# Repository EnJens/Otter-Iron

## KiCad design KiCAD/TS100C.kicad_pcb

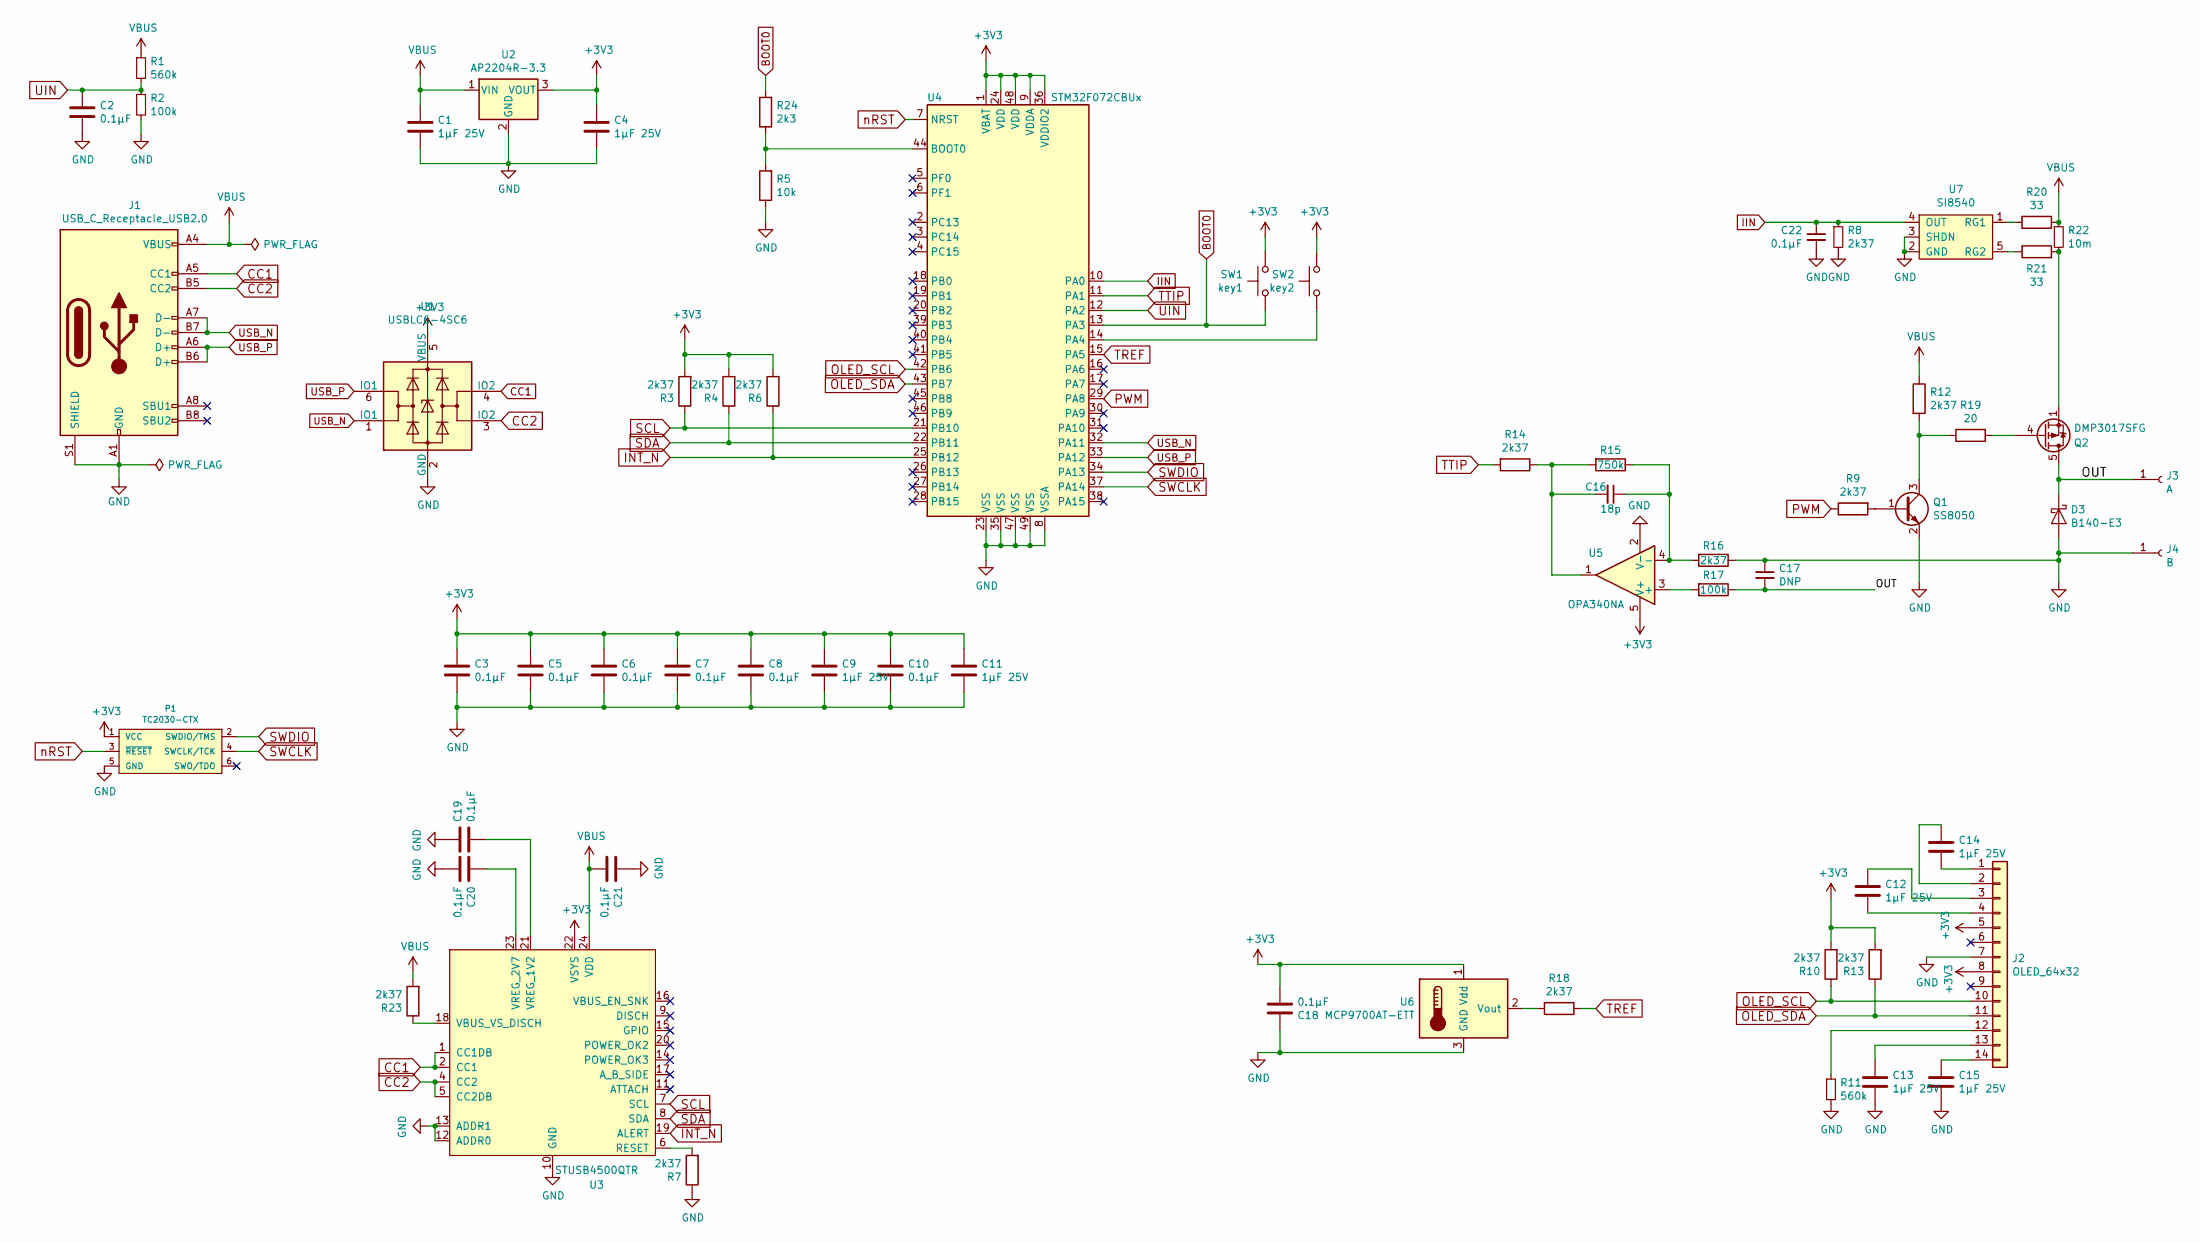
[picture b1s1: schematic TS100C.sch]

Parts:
C1, C4, C9, C11: 1μF 25V; C_0603_1608Metric
C2, C3, C5, C6, C7, C8, C10, C18, C19, C20, C21, C22: 0.1μF; C_0402_1005Metric
C12, C13, C14, C15: 1μF 25V; C_0402_1005Metric
C16: 18p; C_0402_1005Metric
C17: DNP; C_0402_1005Metric
D3: B140-E3; D_SOD-123F
J1: USB_C_Receptacle_USB2.0; USB-C 16Pin
J2: OLED_64x32; 0.69OLED
J3: A; Keystone_3621
J4: B; 3622TR
P1: TC2030-CTX; TC2030-NL_SMALL
Q1: SS8050; SOT-23
Q2: DMP3017SFG; Diodes_PowerDI3333-8
R1, R11: 560k; R_0402_1005Metric
R2, R17: 100k; R_0402_1005Metric
R3, R4, R6, R7, R8, R9, R10, R12, R13, R14, R16, R18, R23: 2k37; R_0402_1005Metric
R5: 10k; R_0402_1005Metric
R15: 750k; R_0402_1005Metric
R19: 20; R_0402_1005Metric
R20, R21: 33; R_0402_1005Metric
R22: 10m; R_0805_2012Metric
R24: 2k3; R_0402_1005Metric
SW1: key1; SW_SPST_PTS810
SW2: key2; SW_SPST_PTS810
U1: USBLC6-4SC6; SOT-23-6
U2: AP2204R-3.3; SOT-89-3
U3: STUSB4500QTR; QFN-24-1EP_4x4mm_P0.5mm_EP2.7x2.7mm
U4: STM32F072CBUx; QFN-48-1EP_7x7mm_P0.5mm_EP5.6x5.6mm
U5: OPA340NA; SOT-23-5
U6: MCP9700AT-ETT; SOT-23
U7: SI8540; SOT-23-5

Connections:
+3V3: C3.1, C4.1, C5.1, C6.1, C7.1, C8.1, C9.1, C10.1, C11.1, C18.1, J2.5, J2.8, P1.1 (VCC), R3.2, R4.2, R6.2, R10.2, R13.2, SW1.1, SW2.1, U1.5 (VBUS), U2.3 (VOUT), U3.22 (VSYS), U4.1 (VBAT), U4.9 (VDDA), U4.24 (VDD), U4.36 (VDDIO2), U4.48 (VDD), U5.5 (V+), U6.1 (Vdd)
/OUT: C17.2, D3.1 (K), J3.1, Q2.5 (D), R17.1
BOOT0: R24.2, SW1.2, U4.13 (PA3)
CC1: J1.A5 (CC1), U1.4 (IO2), U3.1 (CC1DB), U3.2 (CC1)
CC2: J1.B5 (CC2), U1.3 (IO2), U3.4 (CC2), U3.5 (CC2DB)
GND: C1.2, C2.2, C3.2, C4.2, C5.2, C6.2, C7.2, C8.2, C9.2, C10.2, C11.2, C13.2, C15.2, C17.1, C18.2, C19.1, C20.2, C21.1, C22.2, D3.2 (A), J1.A1 (GND), J1.A12 (GND), J1.B1 (GND), J1.B12 (GND), J1.S1 (SHIELD), J2.7, J4.1, P1.5 (GND), Q1.2 (E), R2.2, R5.1, R7.1, R8.2, R11.2, R16.1, U1.2 (GND), U2.2 (GND), U3.10 (GND), U3.12 (ADDR0), U3.13 (ADDR1), U3.25 (GND), U4.8 (VSSA), U4.23 (VSS), U4.35 (VSS), U4.47 (VSS), U4.49 (VSS), U5.2 (V-), U6.3 (GND), U7.2 (GND), U7.3 (SHDN)
IIN: C22.1, R8.1, U4.10 (PA0), U7.4 (OUT)
INT_N: R6.1, U3.19 (ALERT), U4.25 (PB12)
unnamed: C12.1, J2.3
unnamed: C12.2, J2.4
unnamed: C13.1, J2.13
unnamed: C14.1, J2.2
unnamed: C14.2, J2.1
unnamed: C15.1, J2.14
unnamed: C16.1, R15.1, R16.2, U5.4 (-)
unnamed: C16.2, R14.1, R15.2, U5.1
unnamed: C19.2, U3.21 (VREG_1V2)
unnamed: C20.1, U3.23 (VREG_2V7)
unnamed: J2.12, R11.1
unnamed: Q1.1 (B), R9.2
unnamed: Q1.3 (C), R12.2, R19.1
unnamed: Q2.1 (S), Q2.2 (S), Q2.3 (S), R21.2, R22.2
unnamed: Q2.4 (G), R19.2
unnamed: R7.2, U3.6 (RESET)
unnamed: R17.2, U5.3 (+)
unnamed: R18.2, U6.2 (Vout)
unnamed: R20.2, U7.1 (RG1)
unnamed: R21.1, U7.5 (RG2)
unnamed: R23.1, U3.18 (VBUS_VS_DISCH)
unnamed: R5.2, R24.1, U4.44 (BOOT0)
unnamed: SW2.2, U4.14 (PA4)
OLED_SCL: J2.10, R10.1, U4.42 (PB6)
OLED_SDA: J2.11, R13.1, U4.43 (PB7)
PWM: R9.1, U4.29 (PA8)
SCL: R3.1, U3.7 (SCL), U4.21 (PB10)
SDA: R4.1, U3.8 (SDA), U4.22 (PB11)
SWCLK: P1.4 (SWCLK/TCK), U4.37 (PA14)
SWDIO: P1.2 (SWDIO/TMS), U4.34 (PA13)
TREF: R18.1, U4.15 (PA5)
TTIP: R14.2, U4.11 (PA1)
UIN: C2.1, R1.2, R2.1, U4.12 (PA2)
USB_N: J1.A7 (D-), J1.B7 (D-), U1.1 (IO1), U4.32 (PA11)
USB_P: J1.A6 (D+), J1.B6 (D+), U1.6 (IO1), U4.33 (PA12)
VBUS: C1.1, C21.2, J1.A4 (VBUS), J1.A9 (VBUS), J1.B4 (VBUS), J1.B9 (VBUS), R1.1, R12.1, R20.1, R22.1, R23.2, U2.1 (VIN), U3.24 (VDD)
nRST: P1.3 (~RESET~), U4.7 (NRST)

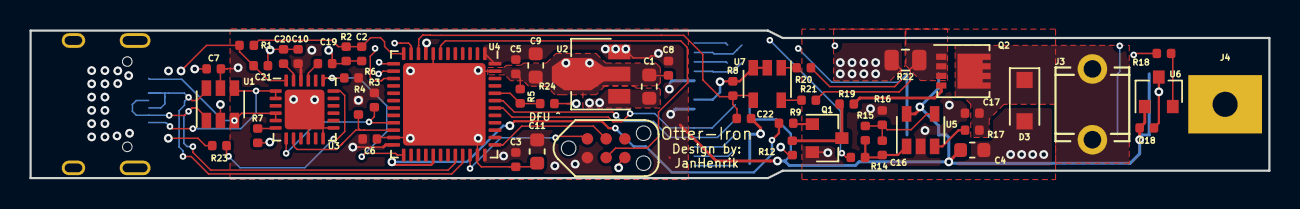
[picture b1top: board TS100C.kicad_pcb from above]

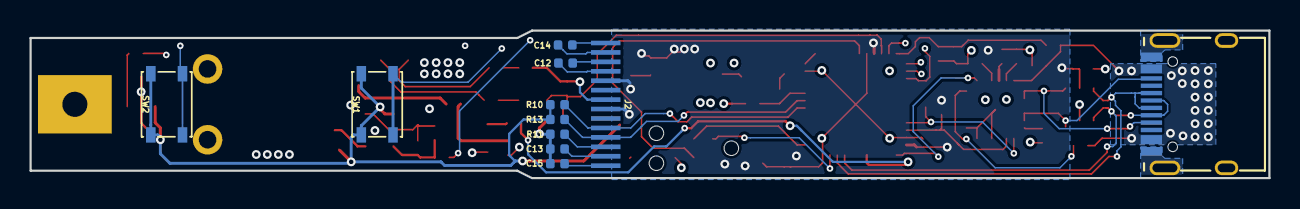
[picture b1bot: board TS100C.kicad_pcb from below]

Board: 4 copper layers, 84.0 x 10.0 mm, 63 parts (11 on the bottom side), 45 nets.

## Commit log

2019-12-27 Hook up SW1 to BOOT0 too
